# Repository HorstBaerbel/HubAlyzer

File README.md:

!!! WORK IN PROGRESS !!!

# HubAlyzer

An ESP32 spectrum analyzer display for HUB75 RGB LED panels and I2S microphones (INMP441). Uses the [ESP32 Arduino core](https://github.com/espressif/arduino-esp32), the [Smartmatrix v4](https://github.com/pixelmatix/SmartMatrix) RGB LED panel library, [my fork](https://github.com/HorstBaerbel/esp32-i2s-slm) of [Ivan Kostoski I2S microphone library](https://github.com/ikostoski/esp32-i2s-slm) and my [development version](https://github.com/HorstBaerbel/arduinoFFT) of the [ArduinoFFT](https://github.com/kosme/arduinoFFT/tree/develop) library.

<p align="center">
    <span>

    </span>
</p>

## Schematics

The circuit is using the SmartMatrix ["forum pinout"](https://github.com/pixelmatix/SmartMatrix/blob/fdb60faf8b140326c75761ac29970e48ac9cc6db/src/MatrixHardware_ESP32_V0.h#L208) without any level shifters for the LED matrix. This is working fine for me for two 32x16 matrices chained together. It includes the "E" pin for driving 64x64 matrices.

<p align="center">
    <span>
        
    </span>
</p>

## Making the PCB

See the [KiCad](KiCad) directory for the PCB files. You can upload the PCB file straight to e.g. [Aisler.net](Aisler.net) and get some pretty PCBs made.

<p align="center">
    <span>
        
    </span>
</p>

## Updating your network configuration

Edit [HubAlyzer/network_config.h](HubAlyzer/network_config.h) and put your WiFi network and password there. Make sure NOT to commit the file and upload to GitHub when forking the repo!

## Problems compiling the Arduino code

Recently there were some problems with SmartMatrix and the ESP32 Arduino libraries, see [this](https://github.com/pixelmatix/SmartMatrix/issues/165).

## Problems flashing the Arduino code

If the Arduino IDE fails to connect to the board / upload the code, see [this](https://github.com/espressif/arduino-esp32/issues/2516).

## License

If you want to build your own soft- or hardware based on this, you can. See the [MIT LICENSE](LICENSE).

## TODO

* Clean up code
* Clean up esp32-i2s-slm fork
* Merge ArduinoFFT master
* More draw functions
* Draw function switching
* Add rotary encoder handling
* And Bluetooth MIDI and/or WiFi interface

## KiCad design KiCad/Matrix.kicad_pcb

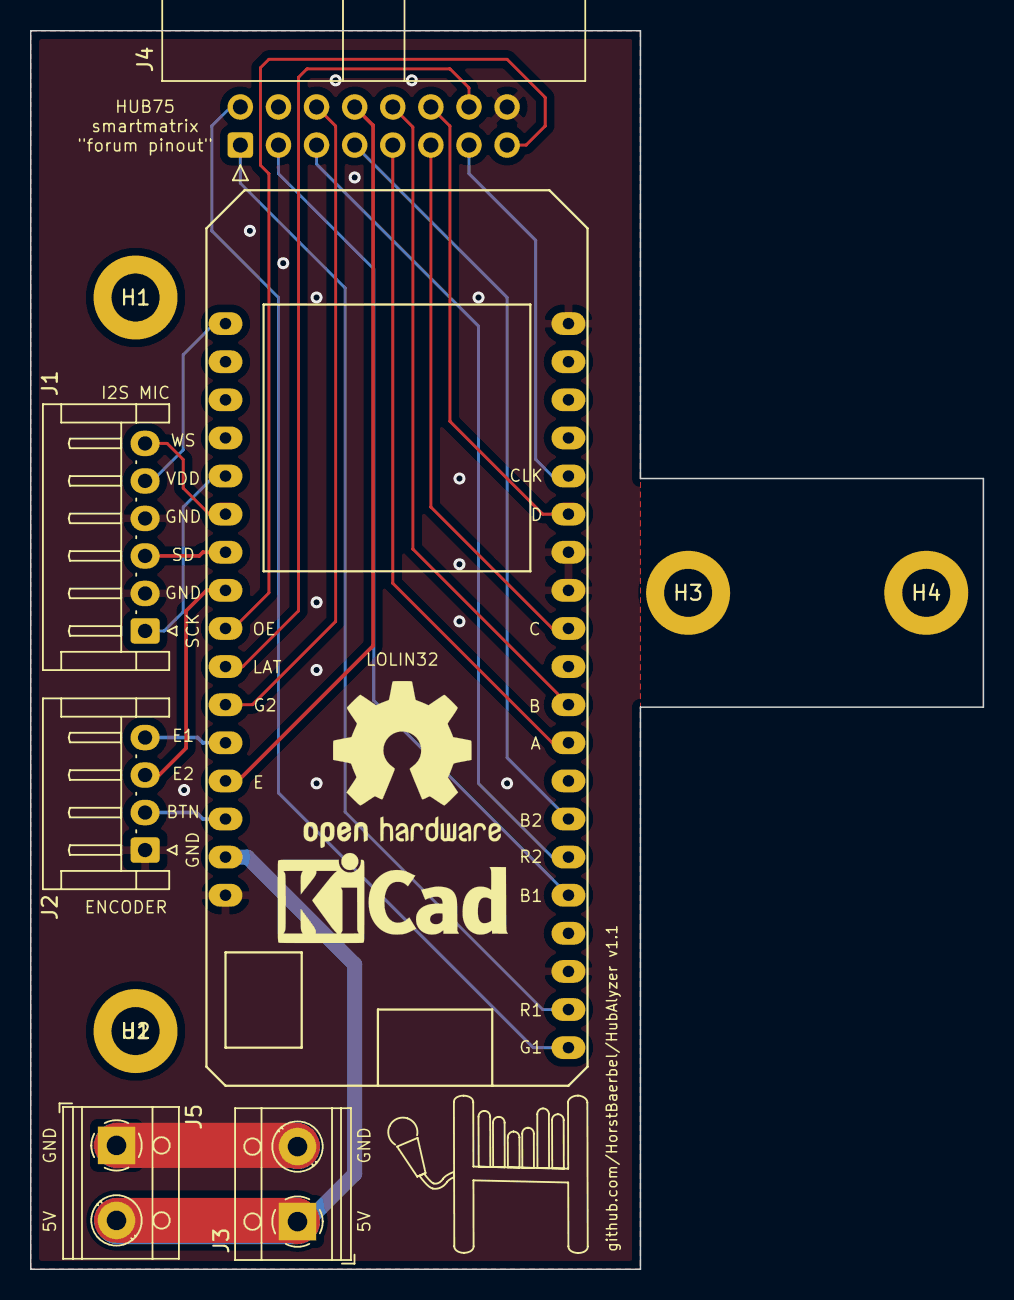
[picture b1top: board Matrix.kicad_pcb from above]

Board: 2 copper layers, 63.5 x 82.5 mm, 12 parts (0 on the bottom side), 23 nets.

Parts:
H1, H2, H3, H4: MountingHole; MountingHole_3.2mm_M3_DIN965_Pad
H5: OH logo; OSHW-Logo2_14.6x12mm_SilkScreen
H6: KiCad logo; KiCad-Logo_6mm_SilkScreen
J1: Conn_01x06_Male; JST_EH_S6B-EH_1x06_P2.50mm_Horizontal
J2: Conn_01x04_Male; JST_EH_S4B-EH_1x04_P2.50mm_Horizontal
J3, J5: Screw_Terminal_01x02; TerminalBlock_RND_205-00012_1x02_P5.00mm_Horizontal
J4: Conn_02x08_Odd_Even; IDC-Header_2x08_P2.54mm_Horizontal
U1: Lolin32

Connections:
+5V: J3.1, J5.2, U1.15
/A: J4.9, U1.28
/B: J4.10, U1.27
/B1: J4.3, U1.32
/B2: J4.7, U1.30
/BTN: J2.2, U1.14
/C: J4.11, U1.25
/CLK: J4.13, U1.21
/D: J4.12, U1.22
/E: J4.8, U1.13
/E1: J2.4, U1.12
/E2: J2.3, U1.8
/G1: J4.2, U1.36
/G2: J4.6, U1.11
/LAT: J4.14, U1.10
/OE: J4.15, U1.9
/R1: J4.1, U1.35
/R2: J4.5, U1.31
/SCK: J1.1, U1.5
/SD: J1.3, U1.7
/VDD: J1.5, U1.1
/WS: J1.6, U1.6
GND: J1.2, J1.4, J2.1, J3.2, J4.4, J4.16, J5.1, U1.16, U1.17, U1.23, U1.24, U1.34

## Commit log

2021-05-28 Add back photo
2021-05-28 Add Arduino sketch
2021-05-28 Add PCB and schematics images
2021-06-09 Move network config to external header
2021-06-09 Make git ignore network_config file
2021-06-22 Update board to use E line
2021-07-19 Add submodules
2021-07-19 Move draw functions to extra file
2021-07-19 Remove submodules from root
2021-07-19 Add submodules to arduino dir
2021-07-19 Fix code and update README
2021-07-20 Some cleanup
2022-07-18 Refactor
2022-07-18 Fix deprecated flags
2022-07-19 Apply a-weighting and add automatic gain control for better spectrum
2022-07-19 Reduce number of samples to improve responsiveness
2022-07-19 Antialised bar drawing
2022-07-21 Refactor: Pass memory from outside into analyzer
2022-07-21 Make peaks darker to improve display
2022-07-22 Refactor: Make FFT a seperate class
2022-08-08 Start to work on beat detection
2022-08-16 Remove FastLED
2022-08-16 Fix normalization and spectrum calculation
2022-08-16 Fix HSVf
2022-08-16 Fiddle with beat detection
2022-08-16 Trying to improve beat detection. Still sucks though...
2022-08-16 Remove library mention. We don't use it anymore
2024-09-02 First working version after refactor
2024-09-02 Fix frame buffer overflow
2024-09-05 Improve beat detection
2024-09-05 Add effect direction control
2024-09-05 Add RGB lerp
2024-09-05 Start to write feedback effects
